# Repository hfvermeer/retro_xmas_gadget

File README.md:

# retro_xmas_gadget
An ESP32S3 based retro gaming handheld running retro-go the open source retro-go, inspired by Megazoid's design on his [CrokPocket](https://www.hackster.io/megazoid/crokpocket-a0ff83).

## Story
This year my niece and nephew, who are 8 and 10 became more aware of what I do for a job as an Embedded Systems Engineer and enthousiastic hobbyist. Each time when there is a family gathering, they ask about 'my inventions', and share with me their ideas what I could invent next. Since they are so interested and we are hosting Christmas this year, I wanted to share a Christmas activity where we can assemble an invention of their own, showing them what electronics can do and giving them a nice memory.

I have stumbled on Megazoid's [design](https://www.hackster.io/megazoid/crokpocket-a0ff83) of his original CrokPocket which I really liked, but I preferred a larger screen. I also had some leftover components such as a few hundred SDHD 4gb memory cards and a stack of 1900mah batteries that I could use for this design to cut cost. And I preferred the CP2102 over the CH340G, and connectors over soldering for the display. Thus the slightly larger CrokPocket XL was born.

Even though this DIY handheld doesn't compare to many linux based emulator machines that are out there, it can't compete to something that you have build yourself. And I actually find that the keypad feels more snappy, I much prefer the shorter throw and click. Featuring the [Retro-Go](https://github.com/ducalex/retro-go) open source firmware I think it can stand on it's own, supporting many games on NES, SNES (slow), Gameboy, Sega Master System, Mega Drive, Game Gear, Colecovision, NEX PC Engine, Atari Lynx and off course, DOOM.

## Instructions

### 1. Ordering

### 2. Soldering

### 3. Flashing

### 4. Printing

### 5. Assembly

## Bill of Materials

## Release Notes

### Changes

* Version 0.9.0
    * Initial 4-layer PCB design

* Version 1.0.0
    * Correct ESP32-S3 footprint, apply keepout area to inner layers
    * Move Screw holes to corners
    * Add Load-sharing Circuit for charging

* Version 1.1.0
    * Footprint Correction for Q3
    * Change values for thermal protection resistors, R17, R23

* Known Issues
    * Reset when unplugging USB
    * Batt voltage measurement when USB plugged in
    * Guide marking for screen
    * More Decoupling for 3.3V

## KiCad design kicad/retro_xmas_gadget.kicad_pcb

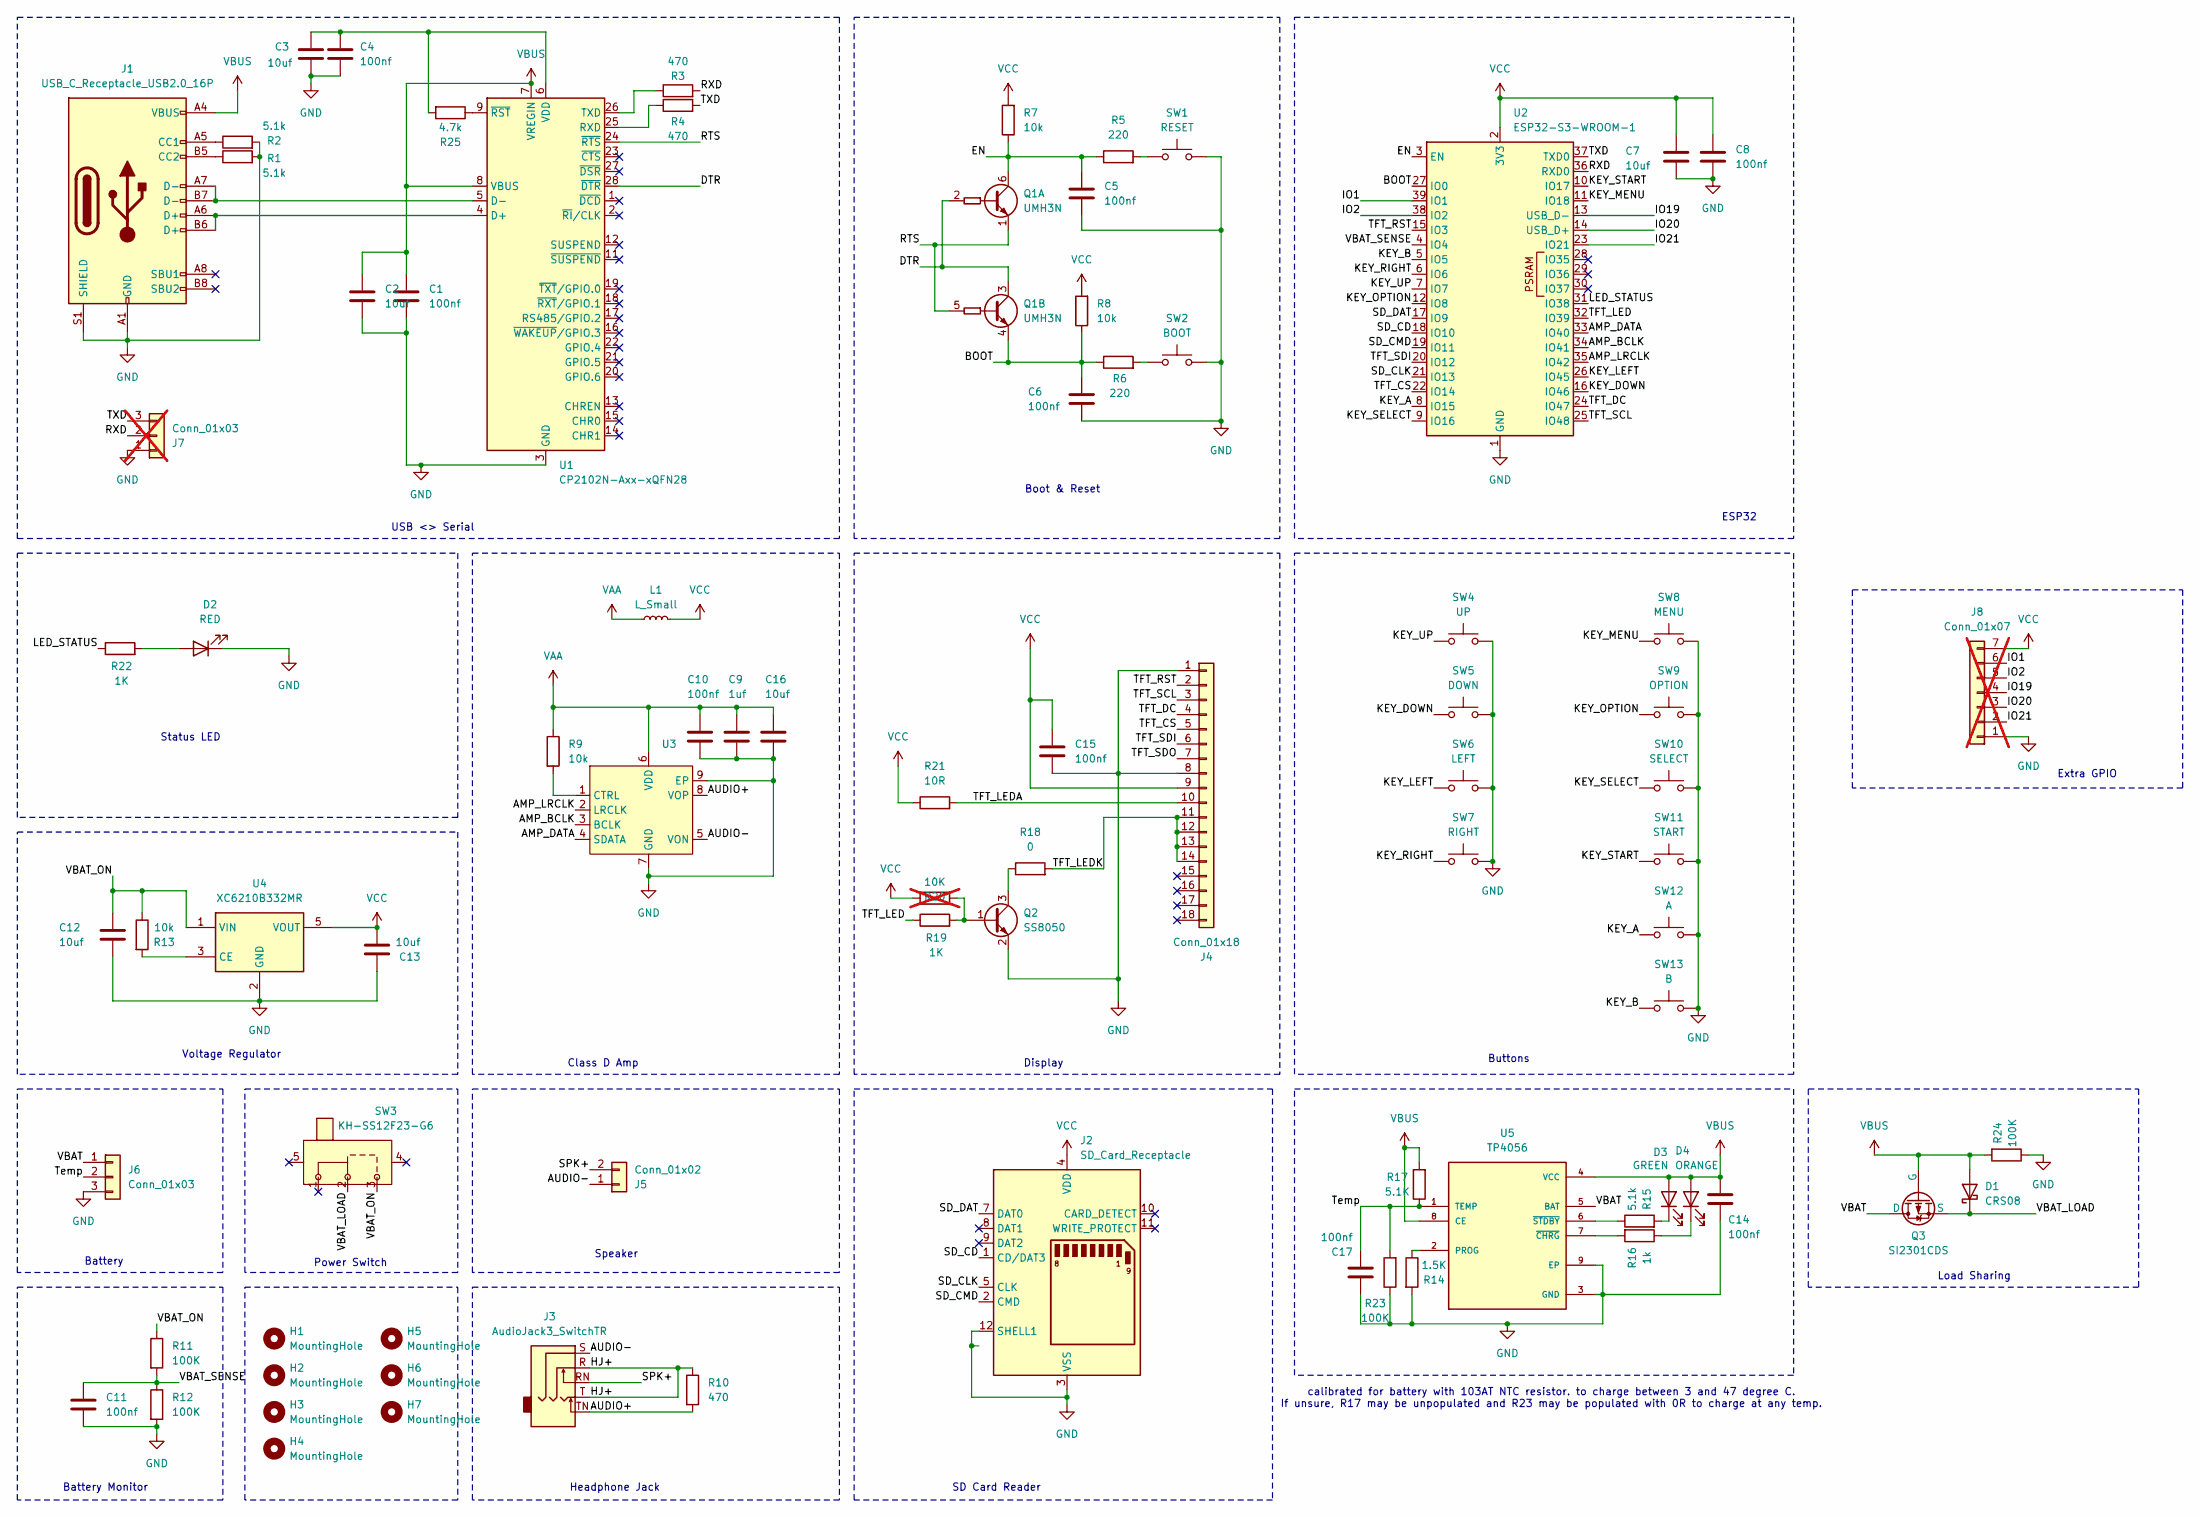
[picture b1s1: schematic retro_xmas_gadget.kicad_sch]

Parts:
C1, C4, C5, C6, C8, C10, C11, C14, C15, C17: 100nf; C_0603_1608Metric_Pad1.08x0.95mm_HandSolder
C2, C3, C7, C12, C13: 10uf; C_0603_1608Metric_Pad1.08x0.95mm_HandSolder
C9: 1uf; C_0603_1608Metric_Pad1.08x0.95mm_HandSolder
C16: 10uf; C_0805_2012Metric_Pad1.18x1.45mm_HandSolder
D1: CRS08; D_SOD-123
D2: RED; LED_0805_2012Metric_Pad1.15x1.40mm_HandSolder
D3: GREEN; LED_0805_2012Metric_Pad1.15x1.40mm_HandSolder
D4: ORANGE; LED_0805_2012Metric_Pad1.15x1.40mm_HandSolder
H1, H2, H3, H4: MountingHole; MountingHole_2.7mm_M2.5
H5, H6: MountingHole; MountingHole_2.5mm
H7: MountingHole; MountingHole_3.5mm
J1: USB_C_Receptacle_USB2.0_16P; USB_C_Receptacle_GCT_USB4105-xx-A_16P_TopMnt_Horizontal
J2: SD_Card_Receptacle; SD_TE_2041021
J3: AudioJack3_SwitchTR; Jack_3.5mm_Ledino_KB3SPRS_Horizontal
J4: Conn_01x18; TE_1-1734839-8_1x18-1MP_P0.5mm_Horizontal
J5: Conn_01x02; AMPHENOL_10114830-10102LF
J6: Conn_01x03; AMPHENOL_10114830-10103LF
J7: Conn_01x03; PinHeader_1x03_P2.54mm_Vertical; not fitted
J8: Conn_01x07; JST_GH_SM07B-GHS-TB_1x07-1MP_P1.25mm_Horizontal; not fitted
L1: L_Small; L_0805_2012Metric_Pad1.05x1.20mm_HandSolder
Q1: UMH3N; SOT-363_SC-70-6
Q2: SS8050; SOT-23
Q3: SI2301CDS; SOT-23_Handsoldering
R1, R2, R15: 5.1k; R_0603_1608Metric_Pad0.98x0.95mm_HandSolder
R3, R4, R10: 470; R_0603_1608Metric_Pad0.98x0.95mm_HandSolder
R5, R6: 220; R_0603_1608Metric_Pad0.98x0.95mm_HandSolder
R7, R8, R9, R13: 10k; R_0603_1608Metric_Pad0.98x0.95mm_HandSolder
R11, R12, R23, R24: 100K; R_0603_1608Metric_Pad0.98x0.95mm_HandSolder
R14: 1.5K; R_0603_1608Metric_Pad0.98x0.95mm_HandSolder
R16: 1k; R_0603_1608Metric_Pad0.98x0.95mm_HandSolder
R17: 5.1K; R_0603_1608Metric_Pad0.98x0.95mm_HandSolder
R18: 0; R_0603_1608Metric_Pad0.98x0.95mm_HandSolder
R19, R22: 1K; R_0603_1608Metric_Pad0.98x0.95mm_HandSolder
R20: 10K; R_0603_1608Metric_Pad0.98x0.95mm_HandSolder; not fitted
R21: 10R; R_0603_1608Metric_Pad0.98x0.95mm_HandSolder
R25: 4.7k; R_0603_1608Metric_Pad0.98x0.95mm_HandSolder
SW1: RESET; SW_Push_SPST_NO_Alps_SKRK
SW2: BOOT; SW_Push_SPST_NO_Alps_SKRK
SW3: KH-SS12F23-G6; SW_Slide_SPDT_Angled_CK_OS102011MA1Q
SW4: UP; SW_SPST_SKQG_WithStem
SW5: DOWN; SW_SPST_SKQG_WithStem
SW6: LEFT; SW_SPST_SKQG_WithStem
SW7: RIGHT; SW_SPST_SKQG_WithStem
SW8: MENU; SW_SPST_SKQG_WithStem
SW9: OPTION; SW_SPST_SKQG_WithStem
SW10: SELECT; SW_SPST_SKQG_WithStem
SW11: START; SW_SPST_SKQG_WithStem
SW12: A; SW_SPST_SKQG_WithStem
SW13: B; SW_SPST_SKQG_WithStem
U1: CP2102N-Axx-xQFN28; QFN-28-1EP_5x5mm_P0.5mm_EP3.35x3.35mm
U2: ESP32-S3-WROOM-1
U3: SOIC-8-1EP_3.9x4.9mm_P1.27mm_EP2.41x3.3mm_ThermalVias
U4: XC6210B332MR; SOT-23-5
U5: TP4056; SOIC-8-1EP_3.9x4.9mm_P1.27mm_EP2.41x3.3mm_ThermalVias

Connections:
/AMP_BCLK: U2.34 (IO41), U3.3 (BCLK)
/AMP_DATA: U2.33 (IO40), U3.4 (SDATA)
/AMP_LRCLK: U2.35 (IO42), U3.2 (LRCLK)
/AUDIO+: J3.TN, R10.2, U3.8 (VOP)
/AUDIO-: J3.S, J5.1, U3.5 (VON)
/BOOT: C6.1, Q1.4 (E2), R6.1, R8.1, U2.27 (IO0)
/DTR: Q1.2 (B1), Q1.3 (C2), U1.28 (~DTR)
/EN: C5.1, Q1.6 (C1), R5.1, R7.1, U2.3 (EN)
/HJ+: J3.R, J3.T, R10.1
/IO1: J8.6, U2.39 (IO1)
/IO2: J8.5, U2.38 (IO2)
/IO19: J8.4, U2.13 (USB_D-)
/IO20: J8.3, U2.14 (USB_D+)
/IO21: J8.2, U2.23 (IO21)
/KEY_A: SW12.1, U2.8 (IO15)
/KEY_B: SW13.1, U2.5 (IO5)
/KEY_DOWN: SW5.1, U2.16 (IO46)
/KEY_LEFT: SW6.1, U2.26 (IO45)
/KEY_MENU: SW8.1, U2.11 (IO18)
/KEY_OPTION: SW9.1, U2.12 (IO8)
/KEY_RIGHT: SW7.1, U2.6 (IO6)
/KEY_SELECT: SW10.1, U2.9 (IO16)
/KEY_START: SW11.1, U2.10 (IO17)
/KEY_UP: SW4.1, U2.7 (IO7)
/LED_STATUS: R22.1, U2.31 (IO38)
/RTS: Q1.1 (E1), Q1.5 (B2), U1.24 (~RTS)
/RXD: J7.2, R3.2, U2.36 (RXD0)
/SD_CD: J2.1 (CD/DAT3), U2.18 (IO10)
/SD_CLK: J2.5 (CLK), U2.21 (IO13)
/SD_CMD: J2.2 (CMD), U2.19 (IO11)
/SD_DAT: J2.7 (DAT0), U2.17 (IO9)
/SPK+: J3.RN, J5.2
/TFT_CS: J4.5, U2.22 (IO14)
/TFT_DC: J4.4, U2.24 (IO47)
/TFT_LED: R19.1, U2.32 (IO39)
/TFT_LEDA: J4.10, R21.2
/TFT_LEDK: J4.11, J4.12, J4.13, J4.14, R18.2
/TFT_RST: J4.2, U2.15 (IO3)
/TFT_SCL: J4.3, U2.25 (IO48)
/TFT_SDI: J4.6, U2.20 (IO12)
/TFT_SDO: J4.7
/TXD: J7.3, R4.2, U2.37 (TXD0)
/Temp: C17.2, J6.2, R17.1, R23.2, U5.1 (TEMP)
/VBAT: J6.1, Q3.2 (D), U5.5 (BAT)
/VBAT_LOAD: D1.1 (K), Q3.3 (S), SW3.2 (B)
/VBAT_ON: C12.2, R11.1, R13.1, SW3.3 (C), U4.1 (VIN)
/VBAT_SENSE: C11.1, R11.2, R12.1, U2.4 (IO4)
GND: C1.2, C2.2, C3.2, C4.2, C5.2, C6.2, C7.2, C8.2, C9.2, C10.2, C11.2, C12.1, C13.2, C14.2, C15.2, C16.2, C17.1, D2.1 (K), J1.A1 (GND), J1.A12 (GND), J1.B1 (GND), J1.B12 (GND), J1.S1 (SHIELD), J2.3 (VSS), J2.6 (VSS), J2.12 (SHELL1), J4.1, J4.8, J6.3, J7.1, J8.1, Q2.2 (E), R1.2, R2.2, R12.2, R14.2, R23.1, R24.1, SW1.2, SW2.2, SW4.2, SW5.2, SW6.2, SW7.2, SW8.2, SW9.2, SW10.2, SW11.2, SW12.2, SW13.2, U1.3 (GND), U1.29 (GND), U2.1 (GND), U2.40 (GND), U2.41 (GND), U3.7 (GND), U3.9 (EP), U4.2 (GND), U5.3 (GND), U5.9 (EP)
unnamed: D2.2 (A), R22.2
unnamed: D3.1 (K), R15.2
unnamed: D4.1 (K), R16.1
unnamed: J1.A5 (CC1), R2.1
unnamed: J1.B5 (CC2), R1.1
unnamed: Q2.1 (B), R19.2, R20.1
unnamed: Q2.3 (C), R18.1
unnamed: R5.2, SW1.1
unnamed: R6.2, SW2.1
unnamed: J1.A6 (D+), J1.B6 (D+), U1.4 (D+)
unnamed: J1.A7 (D-), J1.B7 (D-), U1.5 (D-)
unnamed: R4.1, U1.25 (RXD)
unnamed: R3.1, U1.26 (TXD)
unnamed: C3.1, C4.1, R25.2, U1.6 (VDD)
unnamed: R25.1, U1.9 (~RST)
unnamed: R9.2, U3.1 (CTRL)
unnamed: R13.2, U4.3 (CE)
unnamed: R14.1, U5.2 (PROG)
unnamed: R16.2, U5.7 (~CHRG)
unnamed: R15.1, U5.6 (~STDBY)
VAA: C9.1, C10.1, C16.1, L1.1, R9.1, U3.6 (VDD)
VBUS: C1.1, C2.1, C14.1, D1.2 (A), D3.2 (A), D4.2 (A), J1.A4 (VBUS), J1.A9 (VBUS), J1.B4 (VBUS), J1.B9 (VBUS), Q3.1 (G), R17.2, R24.2, U1.7 (VREGIN), U1.8 (VBUS), U5.4 (VCC), U5.8 (CE)
VCC: C7.1, C8.1, C13.1, C15.1, J2.4 (VDD), J4.9, J8.7, L1.2, R7.2, R8.2, R20.2, R21.1, U2.2 (3V3), U4.5 (VOUT)

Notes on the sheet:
Voltage Regulator
Battery Monitor
Headphone Jack
Battery
Status LED
ESP32
Load Sharing
Display
Speaker
USB <> Serial
Boot & Reset
Class D Amp
SD Card Reader
Buttons
Extra GPIO
Power Switch
calibrated for battery with 103AT NTC resistor. to charge between 3 and 47 degree C. If unsure, R17 may be unpopulated and R23 may be populated with 0R to charge at any temp.

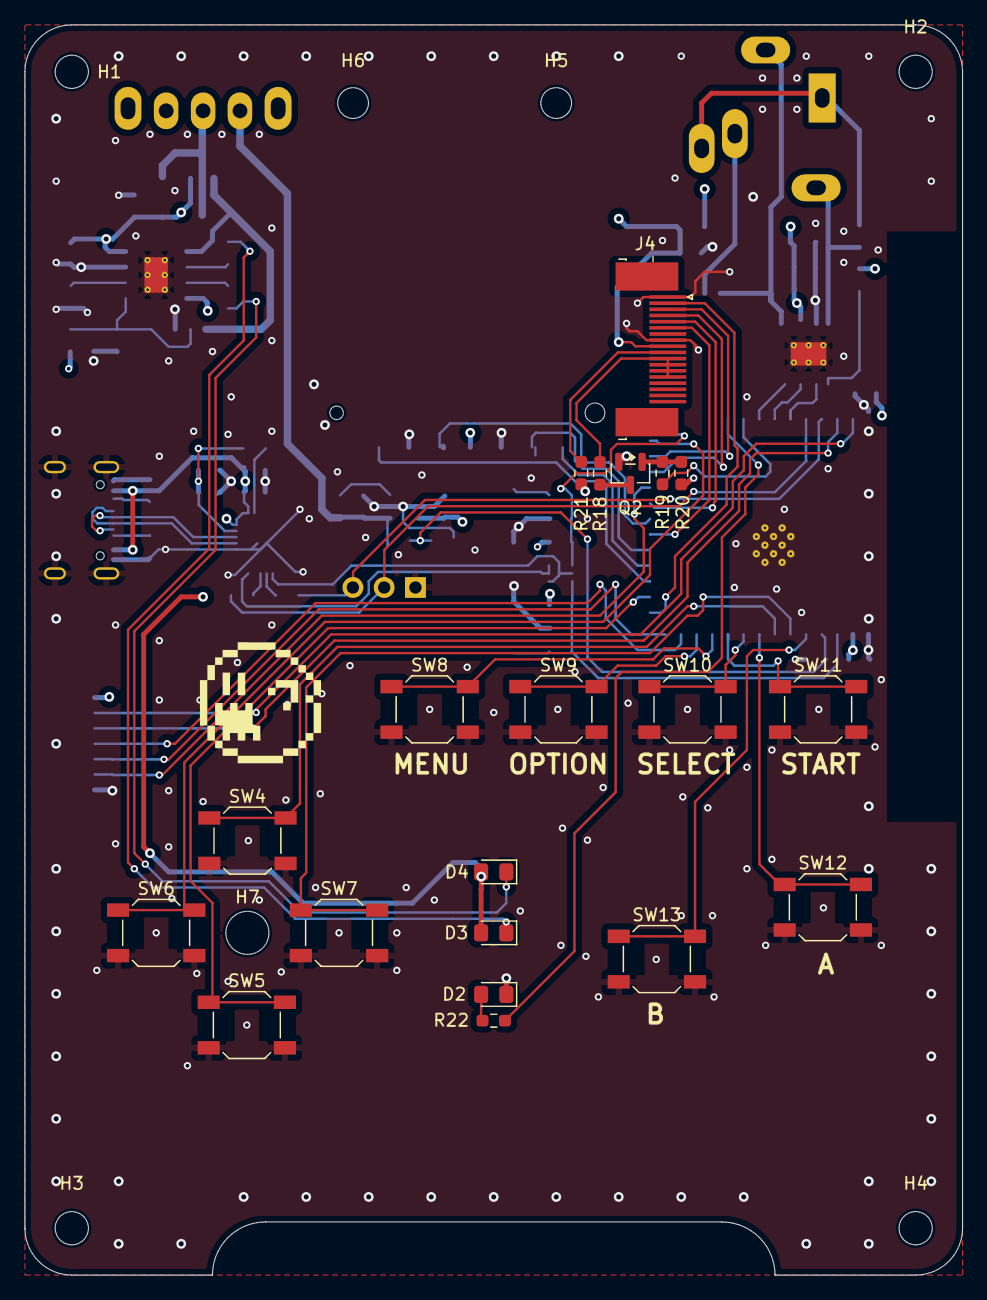
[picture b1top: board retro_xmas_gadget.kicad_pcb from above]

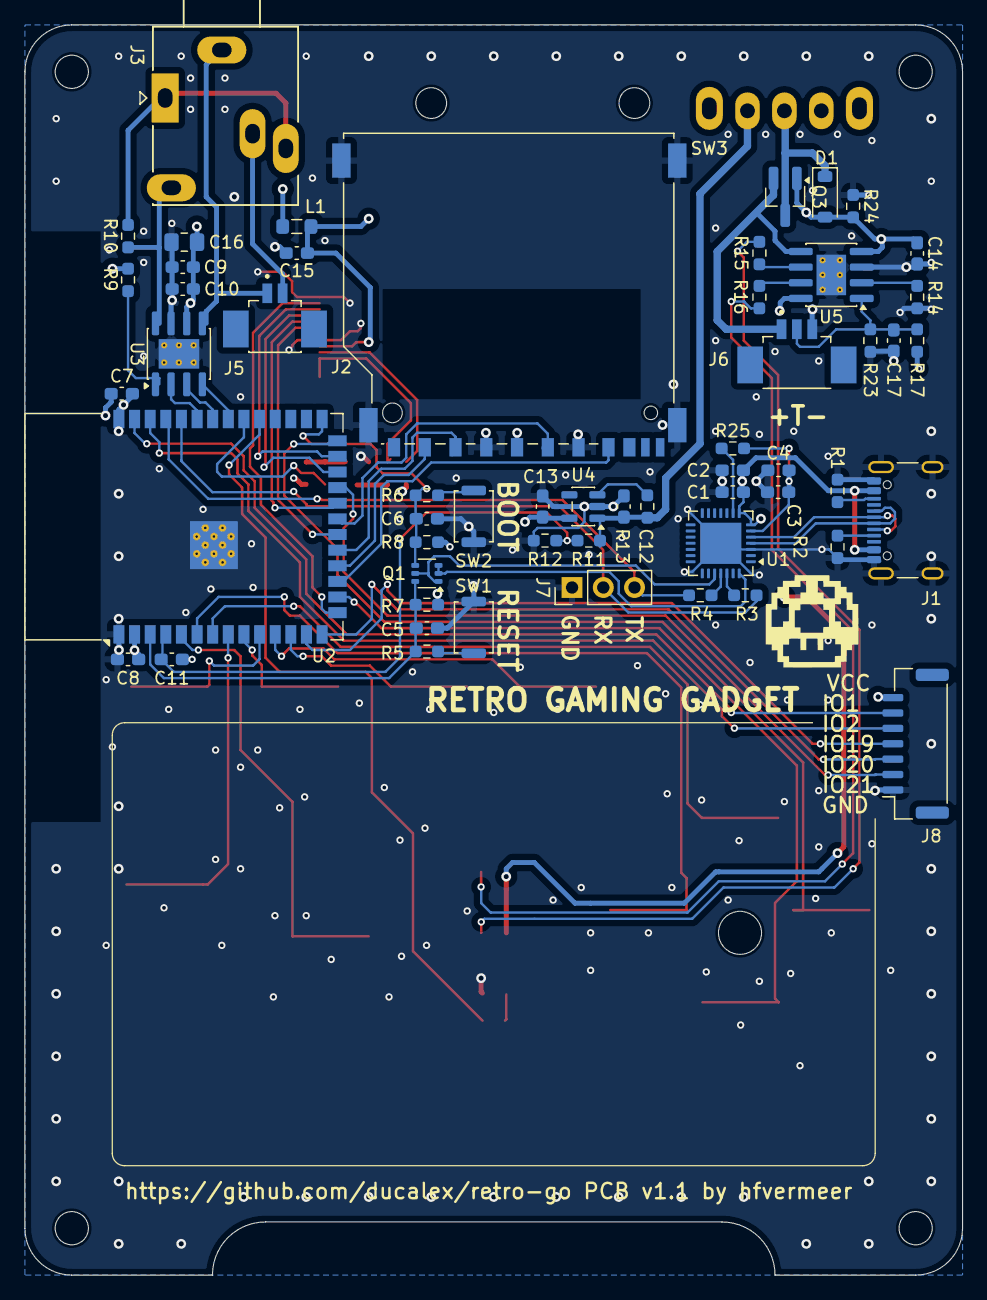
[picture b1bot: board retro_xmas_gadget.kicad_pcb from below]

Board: 4 copper layers, 76.2 x 101.6 mm, 83 parts (56 on the bottom side), 70 nets.

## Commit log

2025-10-25 kicad project
2025-10-25 initial schematic and board layoujt wip
2025-10-26 complete most of design
2025-10-26 initial board layout
2025-10-27 button positioning and routing
2025-10-27 stitching
2025-10-27 moar stitching
2025-10-27 some DRC
2025-10-27 change to 4 layer pcb
2025-10-28 adjustments with 3d model
2025-10-28 baby progress
2025-10-28 mayor checks
2025-10-29 almost complete
2025-10-29 run down checking points
2025-10-30 final improvements and checks
2025-10-30 speaker placement
2025-10-31 final design, with decals
2025-11-09 3d model updates
2025-11-09 keep out inner layers
2025-11-13 Added ESP32-P4, added L,R,X and Y buttons
2025-11-13 improvements and corrections
2025-11-14 update charging resistor
2025-11-14 load sharing
2025-11-15 rearrangement, updates, upgrades
2025-11-15 add pull up resistor to cp2102 rst
2025-11-16 design check. Gerbers
2025-12-08 footprint correction
2025-12-08 add Readme.md
2025-12-08 typo
2025-12-08 text addition
2025-12-08 Add STL's, Firmware
2025-12-16 issues
2026-01-19 component change
